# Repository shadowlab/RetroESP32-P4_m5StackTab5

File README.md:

<div align="center">

# 🕹️ RetroESP32-P4

### Fifteen game consoles and native PC-era shooters — on a single ESP32-P4 microcontroller.

**No GPU. No Linux. Bare-metal RISC-V.**

</div>

---

RetroESP32-P4 is an open-source retro-gaming and application platform built on the **ESP32-P4** — a dual-core RISC-V microcontroller with no dedicated GPU. Grown out of a revival of the original [RetroESP32](https://github.com/retro-esp32/RetroESP32), it brings a modern touchscreen launcher, **15 emulators**, and **native apps that execute from PSRAM** — including full Doom and Quake.

The headline: SNES, Genesis/Mega Drive and the mighty **NeoGeo** all run at **60 FPS**.

---

## ✨ Highlights

- 🎮 **15 emulators** — NES through NeoGeo, all with save/load states
- ⚡ **60 FPS** on the 16-bit heavyweights (SNES, Genesis, NeoGeo)
- 🧩 **Native apps from PSRAM** — Doom, Quake, Duke Nukem 3D, OpenTyrian
- 🖥️ **4.3″ touchscreen handheld** — the Guition ESP32-P4 LCD module
- 🎛️ **Any USB gamepad** — auto-detected and auto-mapped on first use
- 💾 **Save states** on every core, some accessible in-game
- 📦 **Everything included** — firmware, source, SD files, apps, PCB, schematic, and case STLs

---

## 🎮 Supported Emulators

| Family | Systems |
|--------|---------|
| **Nintendo** | NES · Game Boy · Game Boy Color · **SNES** ⭐ |
| **Sega** | Master System · Game Gear · **Genesis / Mega Drive** ⭐ |
| **Arcade** | **NeoGeo** ⭐ |

⭐ = hand-tuned to hold **60 FPS** on the P4.

### ⚡ Performance

- Most systems run at **60 FPS with no frame-skip**.
- **SNES / Genesis** — locked 60 FPS via a real-time frame pacer (a handful of *rendered* frames may drop under heavy load; game logic and audio stay at full speed, so play feels perfectly smooth).
- **NeoGeo** — 60 FPS, fully operational, fed by a sprite cache with batched bank prefetch.

### 💾 Save States

**All** emulators support Save / Load states — several directly from the in-game menu.

---

## 🎛️ Controllers

Plug in **any** USB controller and automatic button mapping starts on first use.

---

## 🖥️ Supported Hardware

### 1. Guition ESP32-P4 4.3″ LCD — the handheld

A single [480×800 touchscreen module](https://www.guition.com/esp32p4-display-module/esp32p4-display) becomes a full handheld (the one pictured up top, in a 3D-printed shell). Available on AliExpress or from Guition.

### 2. M5Stack Tab5 — the tablet

The **M5Stack Tab5** (ESP32-P4, 5″ 720×1280 touchscreen, USB-A host port) is supported as a second target. The
launcher and emulators render straight into the panel's DSI frame buffer (UI 1.25×, emulators 3×), with an
**on-screen touch pad** (D-pad, A/B/X/Y, L/R, Start/Select, Menu, Volume) in the side bars; USB controllers
work too. Not yet verified on real hardware — see **[TAB5.md](TAB5.md)** for the
hardware map, build steps (`./build_all_tab5.sh`) and a first-boot checklist.

> **Update the ESP32-C6 first.** Before flashing RetroESP on a Tab5, run the separate
> [tab5-p4-c6-sdio-ota](https://github.com/shadowlab/tab5-p4-c6-sdio-ota) updater, which flashes a matching ESP-Hosted 3.x firmware into the C6
> over SDIO. It is its own application, not part of this build: flash it on its own, wait for `[PASS]`, then
> flash RetroESP.

---

## 🧩 Native Apps from PSRAM

Beyond emulators, RetroESP32-P4 runs **native** applications. A compact app format (**PAPP**) loads binaries off the SD card, memory-maps them into PSRAM, and executes them in place through a shared, versioned service ABI — so you can add apps **without reflashing firmware**.

Included:

- **Doom**
- **Quake**
- **Duke Nukem 3D**
- **OpenTyrian**
- Example demo template (build your own)

---

## 🚀 Getting Started

1. Format an SD card to **FAT32**.
2. Copy the contents of **`/SDCARD`** onto it.
3. Build the merged firmware image and flash it to address **`0`** using the [web esptool](https://espressif.github.io/esptool-js/)
   (prebuilt images are no longer kept in the repository):
   - **`RetroESP32_P4_v1.bin`** — handheld / LCD build (`build_all.ps1`)
4. Insert the SD card.
5. Connect a USB controller (or use the built-in console frame).
6. **NeoGeo only:** run the included Python script once to generate the sprite-cache files (script is in the SD-card folder).
7. Power on, pick a system, and play. 🎉

---

## 🧠 Under the Hood

- **One image per emulator** — each core is its own OTA flash partition; the launcher switches the active partition and reboots straight into the game, so every emulator gets the whole chip.
- **PPA hardware scaler** — with no GPU, the P4's on-chip 2D Pixel-Processing Accelerator handles rotation, scaling and format conversion.
- **Execute-in-place apps** — the PAPP loader maps SD-card binaries into PSRAM and calls them through a service vtable.
- **Dual-core scheduling** — hot paths pinned to internal SRAM/IRAM; the second core carries audio and display so game logic keeps pace.

**Silicon:** ESP32-P4 · dual-core RISC-V @ 360 MHz · 32 MB PSRAM · 16 MB flash.

---

## 📦 Repository Contents

- Firmware build scripts
- Full source code
- SD-card files
- Native apps + PAPP template
- Console board production files and schematic
- Case STL files
- **Link to a folder with all needed**: https://drive.google.com/drive/folders/1b3OWLKbuuy3KIyPls8iDnDMXTKGiJoFR?usp=sharing

---

## 🔧 Roadmap

- More emulators
- Better performance
- More native apps
- Improved UI
- Wi-Fi features
- BLE controllers

---

## 🙌 Contributing

This is only **Version 1**. Suggestions, testing results, and pull requests are all welcome. If you build one, share a photo!

---

## 📜 Credits

Based on the original **RetroESP32** project, revived and modernized for the ESP32-P4. With thanks to:

- The original RetroESP32 authors
- The creator of the ESP32-based Atari 800 emulator
- The SNES and Genesis core authors
- The author of the NeoGeo (gngeo) Linux port

## 📄 License

MIT License.

## ⭐ Support

If you like this project:

- ⭐ **Star** the repo
- 🍴 **Fork** it
- 🧑‍💻 **Contribute**

---

> RetroESP32-P4 isn't just another emulator project — it's a demonstration of how far a modern microcontroller can go when it's optimized correctly.

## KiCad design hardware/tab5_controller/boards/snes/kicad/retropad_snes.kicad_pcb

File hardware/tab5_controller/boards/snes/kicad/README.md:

# SNES board — KiCad PCB

A complete KiCad project for the SNES RetroPad (console ID 3): a schematic and a two-layer,
fully routed board, linked to each other. It was made with KiCad 7 and opens in KiCad 7, 8 and
9.

| File | What it is |
|---|---|
| `retropad_snes.kicad_pro` | The KiCad project; open this |
| `retropad_snes.kicad_sch` / `retropad_snes_schematic.pdf` | Schematic (one A3 sheet) and a PDF of it |
| `retropad_snes.kicad_pcb` | The routed board |
| `retropad_snes_bom.csv` | Bill of materials. R8 and R9 are listed as DNP (not fitted). |
| `retropad_snes_drc.rpt` | KiCad DRC report for this board |
| [`../../kicad_gen/`](../../kicad_gen) | Shared generators: `gen_pcb.py`, `gen_sch.py`, `check_netlist.py` and `gen_avrdd_pinmap.py` for every console board |

## What's on it

* **Front:** 13 switches.
  * D-pad, SELECT, START and MENU: 6×6 tact switches.
  * A, B, X, Y: 12×12 tact switches at 45°.
  * L and R: right-angle 6×6 switches (PTS645 footprint) whose actuators come out of the side
    edges.
  * The 2×5 right-angle header J1 to the Tab5. Its pins point up out of the top edge, centred
    26 mm from the left edge.
* **Back:**
  * AVR32DD28-I/SO (SOIC-28) with 100 nF on each VDD pin and on VDDIO2, 4.7 µF bulk, 4.7 k
    I2C pull-ups and a 10 k RESET pull-up.
  * Console-ID resistors R6–R9: 0 Ω on ID0 and ID1 for SNES, R8 and R9 not fitted.
  * UPDI header J2: 3V3, UPDI, GND.
* **Buttons:** each switch connects its own MCU pin to GND, with the MCU's internal pull-up.
  No matrix, no diodes. The 6×6 and 12×12 switches use all four legs: 1–2 to GND, 3–4 to the
  MCU pin (see [Switches](../../README.md#switches)); L and R have two contacts. The slot order (PD1–PD7, PC0–PC3, PF0–PF1) follows the layout's
  button order and matches `firmware_avrdd/pinmap.h`; the table is in
  [`../README.md`](../README.md#pcb-and-schematic). J1 pin 9 (INT) and pin 10 (G9) are not
  connected; the host polls.
* **Outline:**
  * 125 × 55 mm, inset 1.5 mm from the case on each side.
  * Notched 3 mm in at the top corners above y = 46 to clear the latch arms.
  * Two M3 holes, 96 mm apart.
* **Stack-up and rules:**
  * 2 layers, 1.6 mm.
  * 0.25 mm tracks, 0.2 mm clearance, 0.6/0.3 mm vias, 0.3 mm copper-to-edge.
  * GND pour on both layers.

## Checks run

* **DRC:** 0 unconnected pads and no clearance, short or edge errors. The report still lists
  silkscreen warnings (labels overlapping pads or running past the edge where L/R overhang),
  plus "library not configured" notes that only appear on a machine without KiCad's library
  table. All are cosmetic.
* **Schematic vs board:** `check_netlist.py` reports the same 25 nets on each side with 0
  differences.
* **Wiring vs firmware:** every switch lands on the MCU pin the firmware's pin map gives it
  for console ID 3, the straps encode ID 3, and J1 carries M5Stack's P1 pinout.
* **Gerber and drill export:** both succeed.

## Schematic

The schematic covers the same circuit on one A3 sheet:
* **MCU:** the AVR32DD28. KiCad 7 has no AVR DD symbol, so the schematic embeds one derived
  from the pin-compatible AVR32DB28, with pins 13/14/15/19 renamed (PD7, VDD, GND, UPDI/PF7).
* **Tab5 header and UPDI header.**
* **Support parts:** decoupling, I2C pull-ups and the RESET pull-up.
* **Console-ID straps:** R8 and R9 are marked DNP.
* **Mounting holes.**
* **Buttons:** one line per button. 4-leg switches show all four pins: 1–2 to GND, 4–3 to
  K_<button>. L and R are 2-pin: K_<button> → switch → GND.

Nets are named with global labels, so the net names match the board exactly (K_UP and so on,
SCL, SDA, ID0–ID3, AN0/AN1, RESET, UPDI, +3V3, GND).

How it stays in step with the board:
* `gen_sch.py` doesn't keep its own list of connections. It builds the board in memory
  and gives each symbol pin the net of the footprint pad with the same number.
* Each footprint carries its symbol's UUID, so in KiCad **Tools → Update PCB from
  Schematic** matches every part and reports no changes.
* `check_netlist.py snes` exports the schematic netlist with `kicad-cli` and compares it with the
  board pad by pad. Current result: 25 nets on each side, 0 differences.

You can now edit the design in KiCad the normal way, schematic first. Just remember that
re-running the generator scripts overwrites the `.kicad_sch` and `.kicad_pcb` files. Once you
start editing by hand, treat the scripts as the starting point and stop re-running them.

KiCad 7's command line has no ERC, so ERC hasn't been run. When you open the schematic, run
**Inspect → Electrical Rules Checker** once. Expect only notes about the power pins being
driven from the connector (J1 has no power-flag symbol).

## ⚠ Before ordering

These can't be settled from M5Stack's drawings, and getting the first one wrong could put
the Tab5's 5 V rail (pin 6) onto this board's 3.3 V supply:

1. **J1 orientation.** The two header rows end up at different heights once the pins are bent
   up, and either end of the 5-pin row could be pin 1. On a real keyboard, use a multimeter to
   find **pin 5 (3V3)**: it connects to the keyboard MCU's VDD pins and the 100 nF capacitors. Also
   find **pins 2/3/4 (GND)**. Note which physical pin positions they are, seen from the front,
   and compare with J1's pin 1 marker here. In the board as drawn, pin 1 is the lower-left pin
   (front view) and the odd row is the one farther from the edge. If yours differs, flip
   `HEADER_PINS` or the header rotation in `../../kicad_gen/gen_pcb.py` (shared by every board) and regenerate.
2. **J1 height and side.** The header sits on the front side, with the pin rows about 1.5 mm
   and 4 mm above the board. Check that this matches where the Tab5's socket is once the shell
   is designed.
3. **M3 hole height** (`M3_Y`, now 45 mm, an estimate) and **latch-arm length** (the board
   notch starts at y = 46).
4. **L/R switch part.** The footprint is C&K PTS645Vx31 (right-angle). Check the actuator
   length against your shell wall, and design the side openings to match.

## Regenerating

See [`../../README.md`](../../README.md#regenerating). For this board:

```
cd ../../kicad_gen
FREEROUTING_JAR=/path/to/freerouting-1.9.0.jar python3 gen_pcb.py snes --route
python3 gen_sch.py snes
python3 check_netlist.py snes          # schematic vs board: must report 0 differences
```

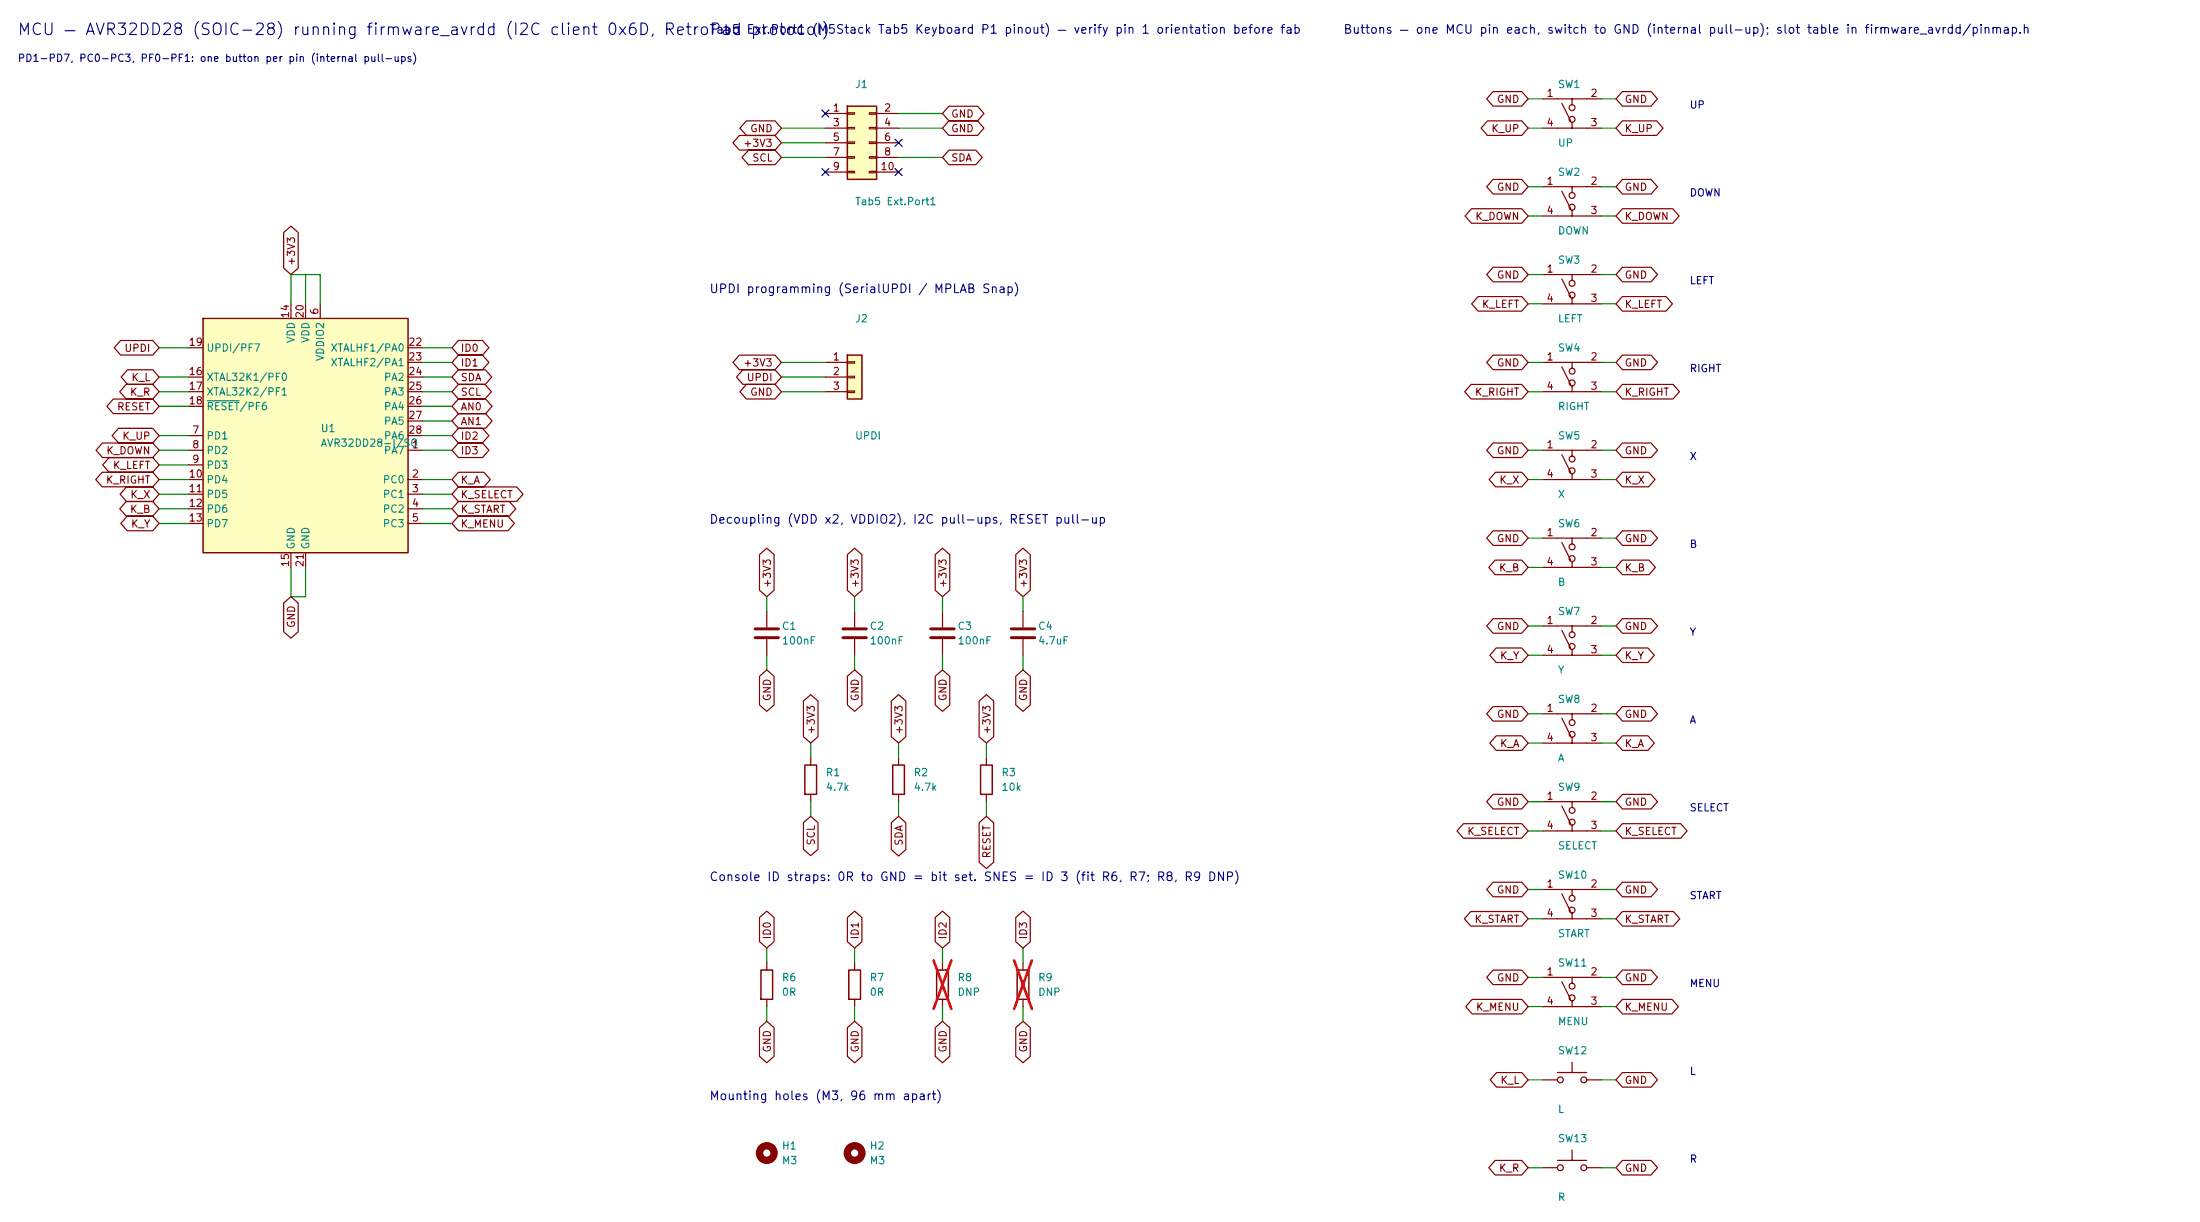
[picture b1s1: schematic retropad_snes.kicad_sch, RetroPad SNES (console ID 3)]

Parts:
C1, C2, C3: 100nF; C_0805_2012Metric_Pad1.18x1.45mm_HandSolder
C4: 4.7uF; C_0805_2012Metric_Pad1.18x1.45mm_HandSolder
H1, H2: M3; MountingHole_3.2mm_M3
J1: Tab5 Ext.Port1; PinHeader_2x05_P2.54mm_Horizontal
J2: UPDI; PinHeader_1x03_P2.54mm_Vertical
R1, R2: 4.7k; R_0805_2012Metric_Pad1.20x1.40mm_HandSolder
R3: 10k; R_0805_2012Metric_Pad1.20x1.40mm_HandSolder
R6, R7: 0R; R_0805_2012Metric_Pad1.20x1.40mm_HandSolder
R8, R9: DNP; R_0805_2012Metric_Pad1.20x1.40mm_HandSolder; not fitted
SW1: UP; SW_PUSH_6mm_4pin
SW2: DOWN; SW_PUSH_6mm_4pin
SW3: LEFT; SW_PUSH_6mm_4pin
SW4: RIGHT; SW_PUSH_6mm_4pin
SW5: X; SW_PUSH-12mm_4pin
SW6: B; SW_PUSH-12mm_4pin
SW7: Y; SW_PUSH-12mm_4pin
SW8: A; SW_PUSH-12mm_4pin
SW9: SELECT; SW_PUSH_6mm_4pin
SW10: START; SW_PUSH_6mm_4pin
SW11: MENU; SW_PUSH_6mm_4pin
SW12: L; SW_Tactile_SPST_Angled_PTS645Vx31-2LFS
SW13: R; SW_Tactile_SPST_Angled_PTS645Vx31-2LFS
U1: AVR32DD28-I/SO; SOIC-28W_7.5x17.9mm_P1.27mm

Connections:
+3V3: C1.1, C2.1, C3.1, C4.1, J1.5, J2.1, R1.1, R2.1, R3.1, U1.6 (VDDIO2), U1.14 (VDD), U1.20 (VDD)
AN0: U1.26 (PA4)
AN1: U1.27 (PA5)
GND: C1.2, C2.2, C3.2, C4.2, J1.2, J1.3, J1.4, J2.3, R6.2, R7.2, R8.2, R9.2, SW1.1, SW1.2, SW2.1, SW2.2, SW3.1, SW3.2, SW4.1, SW4.2, SW5.1, SW5.2, SW6.1, SW6.2, SW7.1, SW7.2, SW8.1, SW8.2, SW9.1, SW9.2, SW10.1, SW10.2, SW11.1, SW11.2, SW12.2, SW13.2, U1.15 (GND), U1.21 (GND)
ID0: R6.1, U1.22 (XTALHF1/PA0)
ID1: R7.1, U1.23 (XTALHF2/PA1)
ID2: R8.1, U1.28 (PA6)
ID3: R9.1, U1.1 (PA7)
K_A: SW8.3, SW8.4, U1.2 (PC0)
K_B: SW6.3, SW6.4, U1.12 (PD6)
K_DOWN: SW2.3, SW2.4, U1.8 (PD2)
K_L: SW12.1, U1.16 (XTAL32K1/PF0)
K_LEFT: SW3.3, SW3.4, U1.9 (PD3)
K_MENU: SW11.3, SW11.4, U1.5 (PC3)
K_R: SW13.1, U1.17 (XTAL32K2/PF1)
K_RIGHT: SW4.3, SW4.4, U1.10 (PD4)
K_SELECT: SW9.3, SW9.4, U1.3 (PC1)
K_START: SW10.3, SW10.4, U1.4 (PC2)
K_UP: SW1.3, SW1.4, U1.7 (PD1)
K_X: SW5.3, SW5.4, U1.11 (PD5)
K_Y: SW7.3, SW7.4, U1.13 (PD7)
RESET: R3.2, U1.18 (~RESET/PF6)
SCL: J1.7, R1.2, U1.25 (PA3)
SDA: J1.8, R2.2, U1.24 (PA2)
UPDI: J2.2, U1.19 (UPDI/PF7)

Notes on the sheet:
MCU — AVR32DD28 (SOIC-28) running firmware_avrdd (I2C client 0x6D, RetroPad protocol)
PD1-PD7, PC0-PC3, PF0-PF1: one button per pin (internal pull-ups)
Tab5 Ext.Port1 (M5Stack Tab5 Keyboard P1 pinout) — verify pin 1 orientation before fab
UPDI programming (SerialUPDI / MPLAB Snap)
Decoupling (VDD x2, VDDIO2), I2C pull-ups, RESET pull-up
Console ID straps: 0R to GND = bit set. SNES = ID 3 (fit R6, R7; R8, R9 DNP)
Mounting holes (M3, 96 mm apart)
Buttons — one MCU pin each, switch to GND (internal pull-up); slot table in firmware_avrdd/pinmap.h
DOWN
LEFT
RIGHT
SELECT
START
MENU

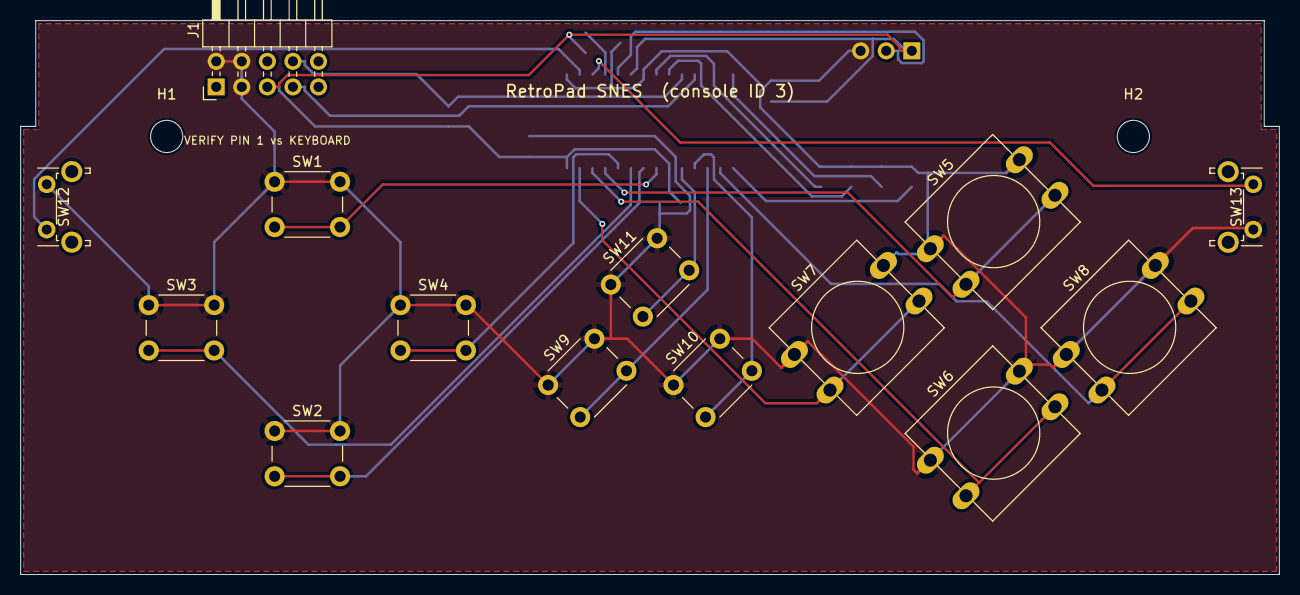
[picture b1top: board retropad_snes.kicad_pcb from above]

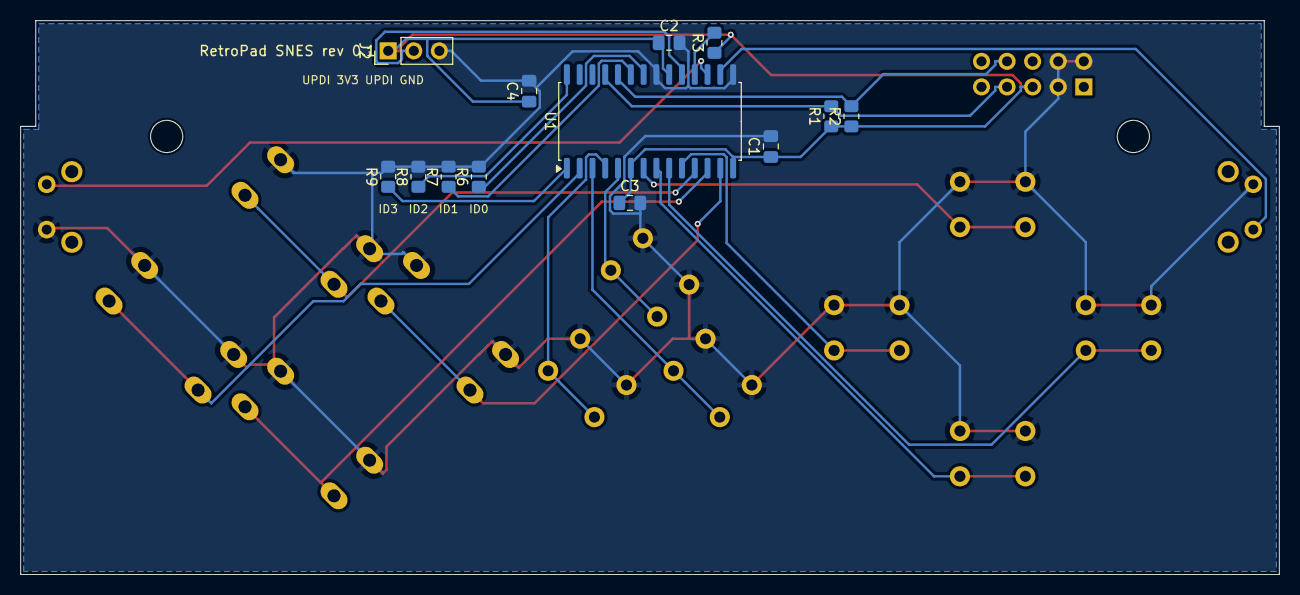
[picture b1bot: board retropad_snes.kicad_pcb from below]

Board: 2 copper layers, 125.0 x 55.0 mm, 29 parts (13 on the bottom side), 23 nets.

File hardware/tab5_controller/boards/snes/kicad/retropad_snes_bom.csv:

Qty,References,Value,Footprint,Side,Fit,Manufacturer,MPN,DigiKey
3,C1 C2 C3,100nF,C_0805_2012Metric_Pad1.18x1.45mm_HandSolder,back,yes,,,
1,C4,4.7uF,C_0805_2012Metric_Pad1.18x1.45mm_HandSolder,back,yes,,,
1,J1,Tab5 Ext.Port1,PinHeader_2x05_P2.54mm_Horizontal,front,yes,Samtec,TSW-105-08-G-D-RA,SAM1037-05-ND
1,J2,UPDI,PinHeader_1x03_P2.54mm_Vertical,back,yes,,,
2,R1 R2,4.7k,R_0805_2012Metric_Pad1.20x1.40mm_HandSolder,back,yes,,,
1,R3,10k,R_0805_2012Metric_Pad1.20x1.40mm_HandSolder,back,yes,,,
2,R6 R7,0R,R_0805_2012Metric_Pad1.20x1.40mm_HandSolder,back,yes,,,
0,R8 R9,DNP,R_0805_2012Metric_Pad1.20x1.40mm_HandSolder,back,DNP,,,
1,SW1,UP,SW_PUSH_6mm_4pin,front,yes,C&K,PTS645SM43-2 LFS,
1,SW2,DOWN,SW_PUSH_6mm_4pin,front,yes,C&K,PTS645SM43-2 LFS,
1,SW3,LEFT,SW_PUSH_6mm_4pin,front,yes,C&K,PTS645SM43-2 LFS,
1,SW4,RIGHT,SW_PUSH_6mm_4pin,front,yes,C&K,PTS645SM43-2 LFS,
1,SW5,X,SW_PUSH-12mm_4pin,front,yes,Omron,B3F-4055,SW414-ND
1,SW6,B,SW_PUSH-12mm_4pin,front,yes,Omron,B3F-4055,SW414-ND
1,SW7,Y,SW_PUSH-12mm_4pin,front,yes,Omron,B3F-4055,SW414-ND
1,SW8,A,SW_PUSH-12mm_4pin,front,yes,Omron,B3F-4055,SW414-ND
1,SW9,SELECT,SW_PUSH_6mm_4pin,front,yes,C&K,PTS645SM43-2 LFS,
1,SW10,START,SW_PUSH_6mm_4pin,front,yes,C&K,PTS645SM43-2 LFS,
1,SW11,MENU,SW_PUSH_6mm_4pin,front,yes,C&K,PTS645SM43-2 LFS,
1,SW12,L,SW_Tactile_SPST_Angled_PTS645Vx31-2LFS,front,yes,C&K,PTS645VL31-2 LFS,CKN9094-ND
1,SW13,R,SW_Tactile_SPST_Angled_PTS645Vx31-2LFS,front,yes,C&K,PTS645VL31-2 LFS,CKN9094-ND
1,U1,AVR32DD28-I/SO,SOIC-28W_7.5x17.9mm_P1.27mm,back,yes,,,

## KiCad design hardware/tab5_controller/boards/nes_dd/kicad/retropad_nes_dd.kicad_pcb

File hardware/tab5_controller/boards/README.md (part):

# RetroPad console boards

Each board is a console-specific controller PCB that fits where the M5Stack Tab5 Keyboard
goes. Every board:
* uses the same AVR32DD28 (SOIC-28), 2×5 Tab5 header and register protocol (see
  [`../README.md`](../README.md));
* wires each button to its own MCU pin (switch to GND, internal pull-up), so there is no key
  matrix and no diodes;
* runs the same firmware, [`../firmware_avrdd`](../firmware_avrdd), programmed over UPDI;
* uses 0805 resistors and capacitors with KiCad's hand-solder pads, so the boards can be
  assembled by hand;
* identifies itself through its console-ID straps, so the firmware maps its buttons for the
  emulator that is running.

| Board | Console ID | Buttons | Layout | KiCad project |
|---|---|---|---|---|
| [SNES](snes/README.md) | 3 | D-pad, A B X Y, L R (side edges), SELECT START, MENU | [svg](snes/layout.svg) | [`snes/kicad`](snes/kicad) |
| [NES / Game Boy / Master System](nes_gb_sms/README.md) | 1, 2 or 4 (CONSOLE button) | D-pad, B A (A raised 4 mm), SELECT START, MENU | [svg](nes_gb_sms/layout.svg) | [`nes_gb_sms/kicad`](nes_gb_sms/kicad) |
| [Genesis / Mega Drive 6-button](genesis/README.md) | 5 | D-pad, X Y Z over A B C, MODE START, MENU | [svg](genesis/layout.svg) | [`genesis/kicad`](genesis/kicad) |

Every KiCad project:
* is a schematic plus a routed, two-layer, 125 × 55 mm PCB;
* passes DRC with 0 unconnected pads and no clearance, short or edge errors (only silkscreen
  warnings remain);
* has a schematic that matches its PCB net for net (`check_netlist.py`).

The SNES layout follows the user's reference drawing. The NES / Game Boy / Master System and
Genesis (6-button) layouts follow each console's own pad, scaled the same way. X/Y/Z/MODE on the
Genesis board reach games through the Genesis core's 6-button support (`components/gwenesis`,
merged from https://github.com/shadowlab/RetroESP32-P4_m5StackTab5/pull/4). The NES / Game Boy / Master System
board puts A 4 mm above B, between the NES pad's level buttons and the Game Boy's diagonal, and
picks its console with a button and an RGB LED (see [Console select](#console-select)).

## How the boards are made

| File | Role |
|---|---|
| [`layout.py`](layout.py) | Button positions for every console, the console IDs, and clearance checks (switch bodies, pads, footprint courtyards, M3 holes, wall margin, latch arms). It also draws `<console>/layout.svg`. |
| [`kicad_gen/gen_pcb.py`](kicad_gen/gen_pcb.py) | Builds the PCB: switches and the 2×5 header on the front; MCU, support parts, console-ID straps and the UPDI header on the back. It routes with Freerouting, pours GND, runs DRC and writes a BOM. |
| [`kicad_gen/gen_sch.py`](kicad_gen/gen_sch.py) | Builds the schematic from the same board data, so it can't drift from the PCB. Every net, GND and +3V3 included, is a global label rather than a KiCad power symbol, so EasyEDA's import keeps the names (it would turn `power:GND` into `power_GND`). |
| [`kicad_gen/check_netlist.py`](kicad_gen/check_netlist.py) | Compares the schematic netlist with the PCB pad by pad |
| [`kicad_gen/render.py`](kicad_gen/render.py) | Writes the front/back/schematic PNGs and the schematic PDF |
| [`kicad_gen/gen_avrdd_pinmap.py`](kicad_gen/gen_avrdd_pinmap.py) | Writes `../firmware_avrdd/pinmap.h`, the per-console button slot table |
| [`kicad_lib/RetroPad.pretty`](kicad_lib/RetroPad.pretty) | 4-pin tact-switch footprints, written by `gen_pcb.py` (see [Switches](#switches)) |

A board has 13 button slots (PD1–PD7, PC0–PC3, PF0–PF1). A console's buttons fill them in
the order its layout lists them. `gen_pcb.py` wires that order, and `gen_avrdd_pinmap.py`
writes it into the firmware's pin map, keyed by console ID. The firmware is therefore the same
for every console; only the ID straps differ.

### Switches

The 6×6 and 12×12 tact switches are 4-leg parts, so the schematics and footprints use all
four pins, numbered like the parts' own symbols:

```
  1 ───┬─── 2      1–2: tied inside the switch  → GND
       /
  4 ───┴─── 3      4–3: tied inside the switch  → K_<button> (MCU pin)
```

* **Footprints:** `RetroPad:SW_PUSH_6mm_4pin` and `RetroPad:SW_PUSH-12mm_4pin` are KiCad's
  `SW_PUSH_6mm` / `SW_PUSH-12mm` with the pads renumbered 1–4. Pad 1 is top-left, then
  clockwise. The tied pairs are the legs 6.5 mm (12.5 mm) apart, as in KiCad's original
  numbering.
* **Symbol:** `RetroPad:SW_Push_4pin`, embedded in each schematic. KiCad's own 4-pin
  `Switch:SW_Push_Dual` is a two-contact switch (1–2 and 3–4 each switched), so it doesn't
  match these parts.
* **L / R (right angle):** two contacts plus two mounting legs, so they keep KiCad's 2-pin
  `SW_Push` and the stock PTS645Vx31 footprint.
* **Other EDA tools:** a vendor's own symbol and footprint can number the legs differently, and
  some parts tie 1–3 / 2–4 instead. Before wiring a part, check its datasheet's
  internal-connection drawing. GND and the MCU pin must go to opposite sides of the contact.
  If they share a tied pair, the button always reads as pressed.

Each board's `kicad/fp-lib-table` points KiCad at `kicad_lib/RetroPad.pretty`.

### Console select

The NES / Game Boy / Master System board serves three consoles. Its ID straps read 14
(`SELECT_STRAP_ID`, never reported to the Tab5), which puts the firmware in select mode:

* **CONSOLE button** (SW_SEL, 6×6 tact switch, front, below SELECT/START) on PC3. Each press
  steps NES (1) → Game Boy (2) → Master System (4) → NES. The firmware reports the new console ID
  at once, and the Tab5 driver re-reads it every 250 ms, so it switches the button map and the
  launcher jumps to that console's games. The choice is saved in EEPROM and restored at power-up
  (a blank EEPROM starts on NES).
* **Status LED** (LED1, OPSCO SK6812MINI-E, reverse mount) shows the console: red = NES,
  green = Game Boy, blue = Master System, at about 16% brightness. It is soldered on the back and
  shines through a 3.3 × 2.9 mm board cutout beside the button. The pads follow the datasheet's
  recommended land pattern (1.8 × 0.82 mm, 0.68 mm gap); a keepout keeps tracks 0.5 mm clear of
  the cutout.
* **LED power:** the SK6812 needs 3.7–5.5 V, so LED1 runs from the Tab5's 5 V (J1 pin 6, unused
  on the other boards) through D1 (1N4148W). The ~4.3 V that leaves lowers the LED's input
  threshold (0.7 × VDD ≈ 3.0 V) enough for the 3.3 V AVR to drive DIN (PC2, through R10 100 Ω)
  in spec. C5 (100 nF) decouples it. The rest of the board stays on 3.3 V; without 5 V on the
  header only the LED stays dark.
* **Timing:** the firmware bit-bangs the LED from a short assembly loop at 24 MHz (0 = 0.29 µs
  high, 1 = 0.63 µs high, 1.25 µs per bit) with interrupts off for about 35 µs. The I2C client
  stretches the clock meanwhile. The colour is re-sent every second in case the LED powered up
  after the MCU.

The console list and colours live in `CONSOLE_SELECT` in `layout.py`; `gen_avrdd_pinmap.py`
copies them into `firmware_avrdd/pinmap.h`.

### Regenerating

```
sudo apt install kicad xvfb default-jre            # KiCad 7+ (with its Python module), Java, virtual display
pip install cairosvg pillow                        # only for render.py
curl -LO https://github.com/freerouting/freerouting/releases/download/v1.9.0/freerouting-1.9.0.jar

cd kicad_gen
export FREEROUTING_JAR=$PWD/../freerouting-1.9.0.jar
for c in snes nes_gb_sms genesis; do
  python3 gen_pcb.py $c --route      # FR_PASSES=300 for more router passes
  python3 gen_sch.py $c
  python3 check_netlist.py $c        # must report 0 differences
  python3 render.py $c
done
python3 gen_avrdd_pinmap.py          # after changing a layout's buttons
```

Freerouting 1.9 runs single-threaded on purpose. In testing, 2.1's multi-threaded optimiser
reported "0 unrouted" but wrote a session with nets missing.

Two changes keep the boards intact through EasyEDA's KiCad import (KiCad shows no difference):
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
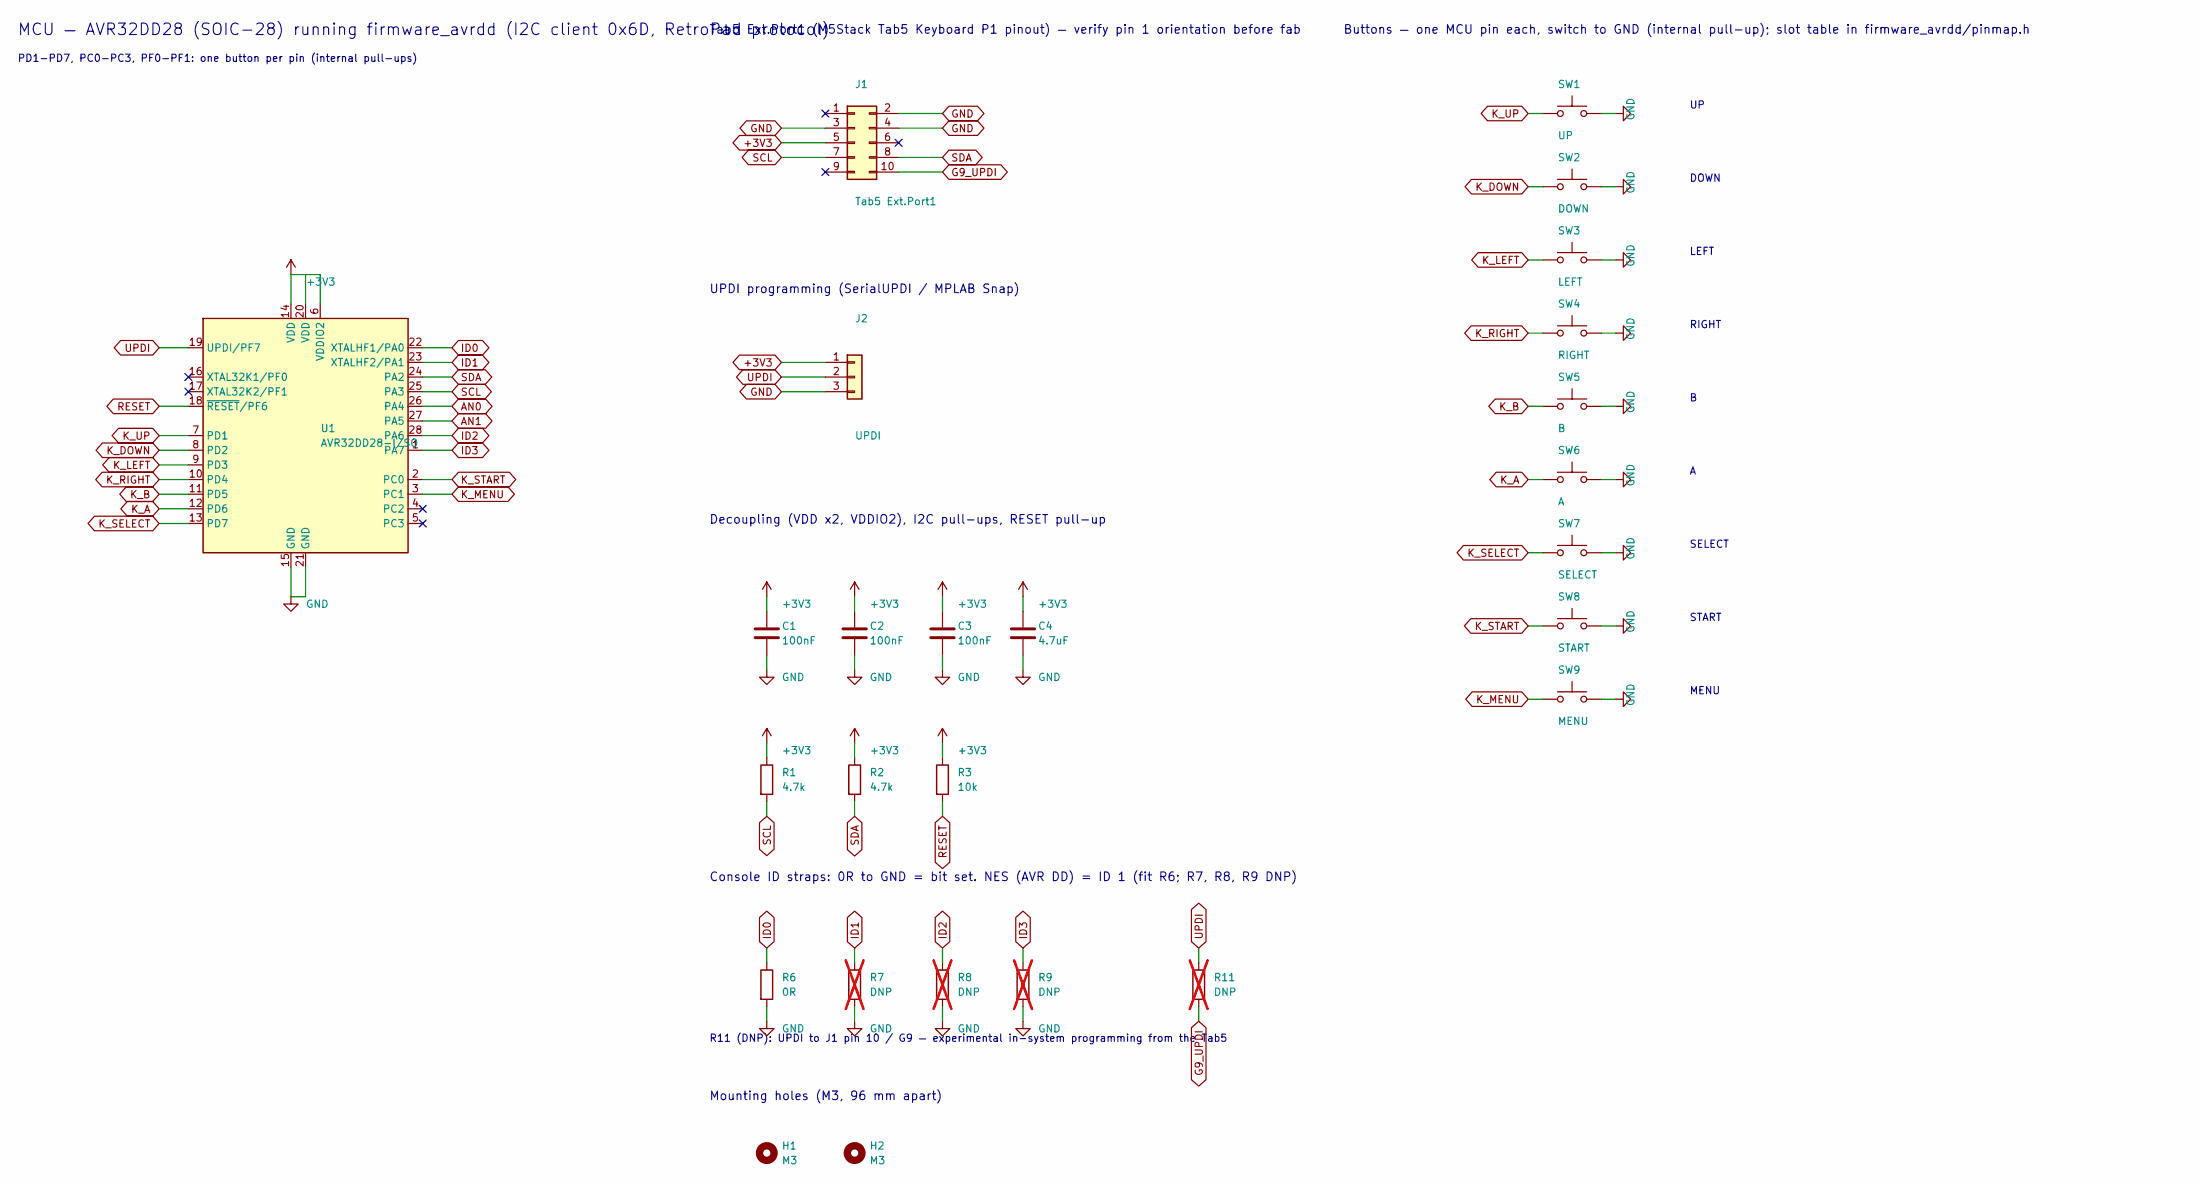
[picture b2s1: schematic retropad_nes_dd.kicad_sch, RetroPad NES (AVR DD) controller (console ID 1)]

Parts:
C1, C2, C3: 100nF; C_0603_1608Metric
C4: 4.7uF; C_0603_1608Metric
H1, H2: M3; MountingHole_3.2mm_M3
J1: Tab5 Ext.Port1; PinHeader_2x05_P2.54mm_Horizontal
J2: UPDI; PinHeader_1x03_P2.54mm_Vertical
R1, R2: 4.7k; R_0603_1608Metric
R3: 10k; R_0603_1608Metric
R6: 0R; R_0603_1608Metric
R7, R8, R9, R11: DNP; R_0603_1608Metric; not fitted
SW1: UP; SW_PUSH_6mm
SW2: DOWN; SW_PUSH_6mm
SW3: LEFT; SW_PUSH_6mm
SW4: RIGHT; SW_PUSH_6mm
SW5: B; SW_PUSH-12mm
SW6: A; SW_PUSH-12mm
SW7: SELECT; SW_PUSH_6mm
SW8: START; SW_PUSH_6mm
SW9: MENU; SW_PUSH_6mm
U1: AVR32DD28-I/SO; SOIC-28W_7.5x17.9mm_P1.27mm

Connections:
+3V3: C1.1, C2.1, C3.1, C4.1, J1.5, J2.1, R1.1, R2.1, R3.1, U1.6 (VDDIO2), U1.14 (VDD), U1.20 (VDD)
AN0: U1.26 (PA4)
AN1: U1.27 (PA5)
G9_UPDI: J1.10, R11.2
GND: C1.2, C2.2, C3.2, C4.2, J1.2, J1.3, J1.4, J2.3, R6.2, R7.2, R8.2, R9.2, SW1.2, SW2.2, SW3.2, SW4.2, SW5.2, SW6.2, SW7.2, SW8.2, SW9.2, U1.15 (GND), U1.21 (GND)
ID0: R6.1, U1.22 (XTALHF1/PA0)
ID1: R7.1, U1.23 (XTALHF2/PA1)
ID2: R8.1, U1.28 (PA6)
ID3: R9.1, U1.1 (PA7)
K_A: SW6.1, U1.12 (PD6)
K_B: SW5.1, U1.11 (PD5)
K_DOWN: SW2.1, U1.8 (PD2)
K_LEFT: SW3.1, U1.9 (PD3)
K_MENU: SW9.1, U1.3 (PC1)
K_RIGHT: SW4.1, U1.10 (PD4)
K_SELECT: SW7.1, U1.13 (PD7)
K_START: SW8.1, U1.2 (PC0)
K_UP: SW1.1, U1.7 (PD1)
RESET: R3.2, U1.18 (~RESET/PF6)
SCL: J1.7, R1.2, U1.25 (PA3)
SDA: J1.8, R2.2, U1.24 (PA2)
UPDI: J2.2, R11.1, U1.19 (UPDI/PF7)

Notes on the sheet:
MCU — AVR32DD28 (SOIC-28) running firmware_avrdd (I2C client 0x6D, RetroPad protocol)
PD1-PD7, PC0-PC3, PF0-PF1: one button per pin (internal pull-ups)
Tab5 Ext.Port1 (M5Stack Tab5 Keyboard P1 pinout) — verify pin 1 orientation before fab
UPDI programming (SerialUPDI / MPLAB Snap)
Decoupling (VDD x2, VDDIO2), I2C pull-ups, RESET pull-up
Console ID straps: 0R to GND = bit set. NES (AVR DD) = ID 1 (fit R6; R7, R8, R9 DNP)
R11 (DNP): UPDI to J1 pin 10 / G9 — experimental in-system programming from the Tab5
Mounting holes (M3, 96 mm apart)
Buttons — one MCU pin each, switch to GND (internal pull-up); slot table in firmware_avrdd/pinmap.h
DOWN
LEFT
RIGHT
SELECT
START
MENU

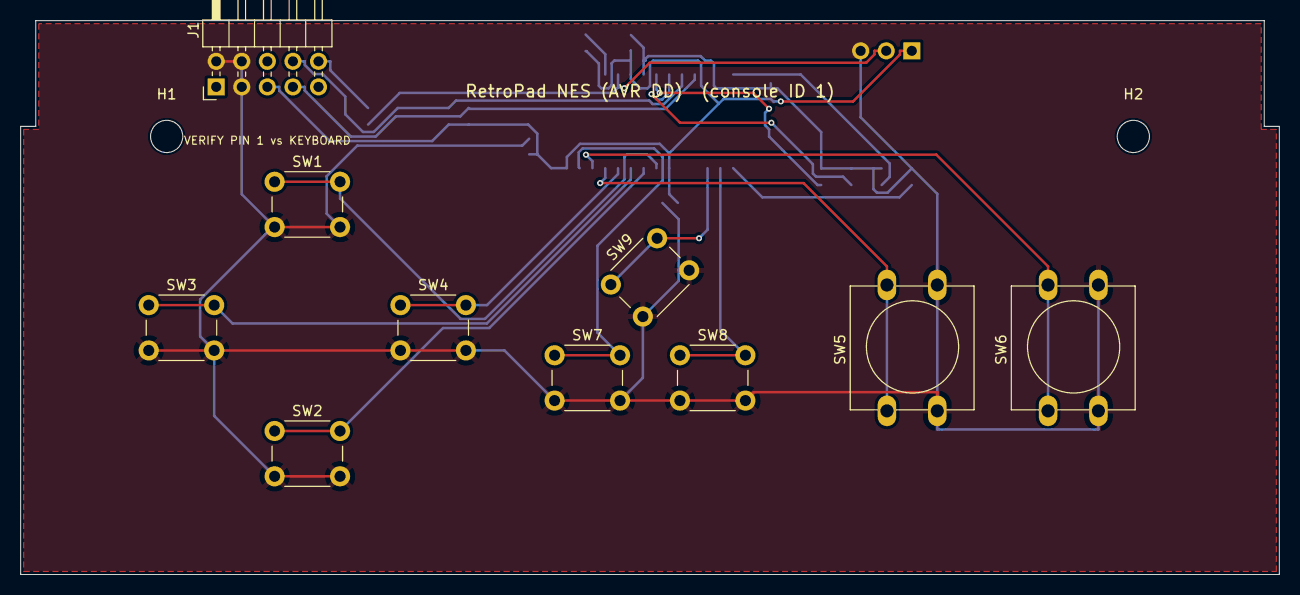
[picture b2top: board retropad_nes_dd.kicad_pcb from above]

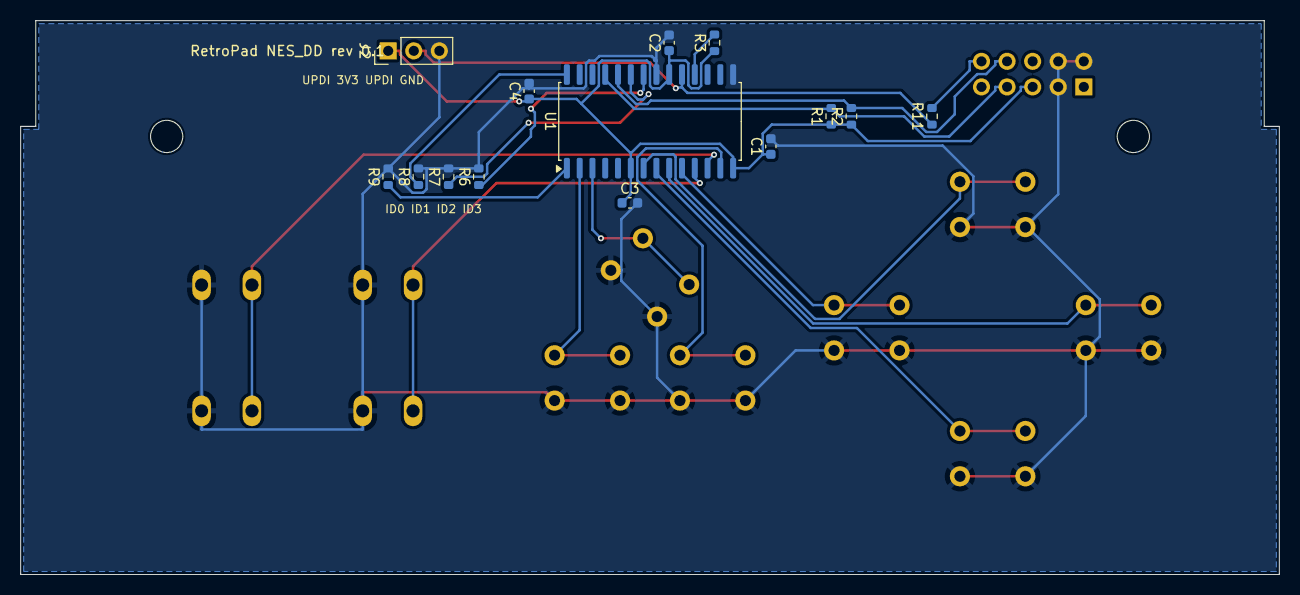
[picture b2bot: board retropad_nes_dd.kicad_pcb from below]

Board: 2 copper layers, 125.0 x 55.0 mm, 26 parts (14 on the bottom side), 20 nets.

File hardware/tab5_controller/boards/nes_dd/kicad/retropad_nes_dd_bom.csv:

Qty,References,Value,Footprint,Side,Fit
3,C1 C2 C3,100nF,C_0603_1608Metric,back,yes
1,C4,4.7uF,C_0603_1608Metric,back,yes
1,J1,Tab5 Ext.Port1,PinHeader_2x05_P2.54mm_Horizontal,front,yes
1,J2,UPDI,PinHeader_1x03_P2.54mm_Vertical,back,yes
2,R1 R2,4.7k,R_0603_1608Metric,back,yes
1,R3,10k,R_0603_1608Metric,back,yes
1,R6,0R,R_0603_1608Metric,back,yes
0,R7 R8 R9 R11,DNP,R_0603_1608Metric,back,DNP
1,SW1,UP,SW_PUSH_6mm,front,yes
1,SW2,DOWN,SW_PUSH_6mm,front,yes
1,SW3,LEFT,SW_PUSH_6mm,front,yes
1,SW4,RIGHT,SW_PUSH_6mm,front,yes
1,SW5,B,SW_PUSH-12mm,front,yes
1,SW6,A,SW_PUSH-12mm,front,yes
1,SW7,SELECT,SW_PUSH_6mm,front,yes
1,SW8,START,SW_PUSH_6mm,front,yes
1,SW9,MENU,SW_PUSH_6mm,front,yes
1,U1,AVR32DD28-I/SO,SOIC-28W_7.5x17.9mm_P1.27mm,back,yes

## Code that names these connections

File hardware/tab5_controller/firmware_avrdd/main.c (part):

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 * keyboard's event/HID/char modes are not.
 *
 * Pins (see boards/layout.py AVRDD_SLOTS and pinmap.h):
 *   PD1-PD7, PC0-PC3, PF0-PF1  13 button slots, switch to GND, internal pull-up
 *   PA2 SDA, PA3 SCL           I2C client to the Tab5 (TWI0 default pins)
 *   PA0, PA1, PA6, PA7         console-ID straps ID0..ID3 (0R to GND = bit set)
 *   PA4, PA5                   AN0 / AN1 (AIN24 / AIN25), Atari paddle/analog boards
 *   PC3, PC2                   console-select boards: select button, SK6812 status LED
 *   PF7 UPDI, PF6 RESET        programming
 */
#include <avr/eeprom.h>
#include <avr/interrupt.h>
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
static uint8_t read_console_id(void)
{
    static const uint8_t strap_pin[4] = {0, 1, 6, 7};     /* PA0, PA1, PA6, PA7 */
    uint8_t id = 0;
    for (uint8_t i = 0; i < 4; i++)
        pullup(&PORTA, strap_pin[i]);
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
/* ── console-select boards (pinmap.h SELECT_*) ─────────────────────────── *
 * Straps reading SELECT_STRAP_ID mark a board shared by several consoles. Each
 * press of the select button (PC3) steps to the next entry of select_console[],
 * which is saved to EEPROM and shown on the SK6812MINI-E on PC2 in that
 * console's colour. The Tab5 re-reads the console ID, so the launcher follows. */
#define SEL_DEBOUNCE_MS 20
#define LED_REFRESH_MS  1000            /* re-send: the LED's 5 V may come up late */
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
static void twi_init(void)
{
    PORTMUX.TWIROUTEA = PORTMUX_TWI0_DEFAULT_gc;             /* SDA PA2, SCL PA3 */
    TWI0.SADDR = RP_I2C_ADDR_DEFAULT << 1;
    TWI0.SCTRLA = TWI_DIEN_bm | TWI_APIEN_bm | TWI_PIEN_bm | TWI_ENABLE_bm;
}
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
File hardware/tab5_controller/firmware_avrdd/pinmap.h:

/* Generated by boards/kicad_gen/gen_avrdd_pinmap.py from boards/layout.py. Do not edit. */
#ifndef RETROPAD_PINMAP_H
#define RETROPAD_PINMAP_H

#include <avr/io.h>
#include "retropad_proto.h"

#define SLOT_COUNT 13
#define SLOT_NONE  0xFF

/* Button slot -> MCU pin (switch to GND, internal pull-up) */
static PORT_t *const slot_port[SLOT_COUNT] = {&PORTD, &PORTD, &PORTD, &PORTD, &PORTD, &PORTD, &PORTD, &PORTC, &PORTC, &PORTC, &PORTC, &PORTF, &PORTF};
static const uint8_t slot_pin[SLOT_COUNT] = {1, 2, 3, 4, 5, 6, 7, 0, 1, 2, 3, 0, 1};

/* Console ID -> RetroPad bit carried by each slot (SLOT_NONE = not fitted) */
static const uint8_t slot_bit[RP_CONSOLE_COUNT][SLOT_COUNT] = {
    /*  0 no board layout yet: generic slot order UP DOWN LEFT RIGHT A B X Y L R SELECT START MENU */
    [0] = {RP_BTN_UP, RP_BTN_DOWN, RP_BTN_LEFT, RP_BTN_RIGHT, RP_BTN_A, RP_BTN_B, RP_BTN_X, RP_BTN_Y, RP_BTN_L, RP_BTN_R, RP_BTN_SELECT, RP_BTN_START, RP_BTN_MENU},
    /*  1 same slots as the NES / Game Boy / Master System board: UP=PD1, DOWN=PD2, LEFT=PD3, RIGHT=PD4, B=PD5, A=PD6, SELECT=PD7, START=PC0, MENU=PC1 */
    [1] = {RP_BTN_UP, RP_BTN_DOWN, RP_BTN_LEFT, RP_BTN_RIGHT, RP_BTN_B, RP_BTN_A, RP_BTN_SELECT, RP_BTN_START, RP_BTN_MENU, SLOT_NONE, SLOT_NONE, SLOT_NONE, SLOT_NONE},
    /*  2 same slots as the NES / Game Boy / Master System board: UP=PD1, DOWN=PD2, LEFT=PD3, RIGHT=PD4, B=PD5, A=PD6, SELECT=PD7, START=PC0, MENU=PC1 */
    [2] = {RP_BTN_UP, RP_BTN_DOWN, RP_BTN_LEFT, RP_BTN_RIGHT, RP_BTN_B, RP_BTN_A, RP_BTN_SELECT, RP_BTN_START, RP_BTN_MENU, SLOT_NONE, SLOT_NONE, SLOT_NONE, SLOT_NONE},
    /*  3 SNES: UP=PD1, DOWN=PD2, LEFT=PD3, RIGHT=PD4, X=PD5, B=PD6, Y=PD7, A=PC0, SELECT=PC1, START=PC2, MENU=PC3, L=PF0, R=PF1 */
    [3] = {RP_BTN_UP, RP_BTN_DOWN, RP_BTN_LEFT, RP_BTN_RIGHT, RP_BTN_X, RP_BTN_B, RP_BTN_Y, RP_BTN_A, RP_BTN_SELECT, RP_BTN_START, RP_BTN_MENU, RP_BTN_L, RP_BTN_R},
    /*  4 same slots as the NES / Game Boy / Master System board: UP=PD1, DOWN=PD2, LEFT=PD3, RIGHT=PD4, B=PD5, A=PD6, SELECT=PD7, START=PC0, MENU=PC1 */
    [4] = {RP_BTN_UP, RP_BTN_DOWN, RP_BTN_LEFT, RP_BTN_RIGHT, RP_BTN_B, RP_BTN_A, RP_BTN_SELECT, RP_BTN_START, RP_BTN_MENU, SLOT_NONE, SLOT_NONE, SLOT_NONE, SLOT_NONE},
    /*  5 Genesis / Mega Drive 6-button: UP=PD1, DOWN=PD2, LEFT=PD3, RIGHT=PD4, A=PD5, X=PD6, B=PD7, Y=PC0, C=PC1, Z=PC2, MODE=PC3, START=PF0, MENU=PF1 */
    [5] = {RP_BTN_UP, RP_BTN_DOWN, RP_BTN_LEFT, RP_BTN_RIGHT, RP_BTN_A, RP_BTN_X, RP_BTN_B, RP_BTN_Y, RP_BTN_C, RP_BTN_Z, RP_BTN_SELECT, RP_BTN_START, RP_BTN_MENU},
    /*  6 no board layout yet: generic slot order UP DOWN LEFT RIGHT A B X Y L R SELECT START MENU */
    [6] = {RP_BTN_UP, RP_BTN_DOWN, RP_BTN_LEFT, RP_BTN_RIGHT, RP_BTN_A, RP_BTN_B, RP_BTN_X, RP_BTN_Y, RP_BTN_L, RP_BTN_R, RP_BTN_SELECT, RP_BTN_START, RP_BTN_MENU},
    /*  7 no board layout yet: generic slot order UP DOWN LEFT RIGHT A B X Y L R SELECT START MENU */
    [7] = {RP_BTN_UP, RP_BTN_DOWN, RP_BTN_LEFT, RP_BTN_RIGHT, RP_BTN_A, RP_BTN_B, RP_BTN_X, RP_BTN_Y, RP_BTN_L, RP_BTN_R, RP_BTN_SELECT, RP_BTN_START, RP_BTN_MENU},
    /*  8 no board layout yet: generic slot order UP DOWN LEFT RIGHT A B X Y L R SELECT START MENU */
    [8] = {RP_BTN_UP, RP_BTN_DOWN, RP_BTN_LEFT, RP_BTN_RIGHT, RP_BTN_A, RP_BTN_B, RP_BTN_X, RP_BTN_Y, RP_BTN_L, RP_BTN_R, RP_BTN_SELECT, RP_BTN_START, RP_BTN_MENU},
    /*  9 no board layout yet: generic slot order UP DOWN LEFT RIGHT A B X Y L R SELECT START MENU */
    [9] = {RP_BTN_UP, RP_BTN_DOWN, RP_BTN_LEFT, RP_BTN_RIGHT, RP_BTN_A, RP_BTN_B, RP_BTN_X, RP_BTN_Y, RP_BTN_L, RP_BTN_R, RP_BTN_SELECT, RP_BTN_START, RP_BTN_MENU},
    /* 10 no board layout yet: generic slot order UP DOWN LEFT RIGHT A B X Y L R SELECT START MENU */
    [10] = {RP_BTN_UP, RP_BTN_DOWN, RP_BTN_LEFT, RP_BTN_RIGHT, RP_BTN_A, RP_BTN_B, RP_BTN_X, RP_BTN_Y, RP_BTN_L, RP_BTN_R, RP_BTN_SELECT, RP_BTN_START, RP_BTN_MENU},
    /* 11 no board layout yet: generic slot order UP DOWN LEFT RIGHT A B X Y L R SELECT START MENU */
    [11] = {RP_BTN_UP, RP_BTN_DOWN, RP_BTN_LEFT, RP_BTN_RIGHT, RP_BTN_A, RP_BTN_B, RP_BTN_X, RP_BTN_Y, RP_BTN_L, RP_BTN_R, RP_BTN_SELECT, RP_BTN_START, RP_BTN_MENU},
    /* 12 no board layout yet: generic slot order UP DOWN LEFT RIGHT A B X Y L R SELECT START MENU */
    [12] = {RP_BTN_UP, RP_BTN_DOWN, RP_BTN_LEFT, RP_BTN_RIGHT, RP_BTN_A, RP_BTN_B, RP_BTN_X, RP_BTN_Y, RP_BTN_L, RP_BTN_R, RP_BTN_SELECT, RP_BTN_START, RP_BTN_MENU},
    /* 13 no board layout yet: generic slot order UP DOWN LEFT RIGHT A B X Y L R SELECT START MENU */
    [13] = {RP_BTN_UP, RP_BTN_DOWN, RP_BTN_LEFT, RP_BTN_RIGHT, RP_BTN_A, RP_BTN_B, RP_BTN_X, RP_BTN_Y, RP_BTN_L, RP_BTN_R, RP_BTN_SELECT, RP_BTN_START, RP_BTN_MENU},
    /* 14 NES / Game Boy / Master System: UP=PD1, DOWN=PD2, LEFT=PD3, RIGHT=PD4, B=PD5, A=PD6, SELECT=PD7, START=PC0, MENU=PC1 */
    [14] = {RP_BTN_UP, RP_BTN_DOWN, RP_BTN_LEFT, RP_BTN_RIGHT, RP_BTN_B, RP_BTN_A, RP_BTN_SELECT, RP_BTN_START, RP_BTN_MENU, SLOT_NONE, SLOT_NONE, SLOT_NONE, SLOT_NONE},
    /* 15 no board layout yet: generic slot order UP DOWN LEFT RIGHT A B X Y L R SELECT START MENU */
    [15] = {RP_BTN_UP, RP_BTN_DOWN, RP_BTN_LEFT, RP_BTN_RIGHT, RP_BTN_A, RP_BTN_B, RP_BTN_X, RP_BTN_Y, RP_BTN_L, RP_BTN_R, RP_BTN_SELECT, RP_BTN_START, RP_BTN_MENU},
};

/* Console-select board (NES / Game Boy / Master System): straps read SELECT_STRAP_ID; the select button
 * (PC3) steps through select_console[], shown on the status LED (PC2) in GRB. */
#define SELECT_STRAP_ID 14
#define SELECT_COUNT 3
static const uint8_t select_console[SELECT_COUNT] = {1 /* NES */, 2 /* GB */, 4 /* SMS */};
static const uint8_t select_grb[SELECT_COUNT][3] = {{0, 40, 0}, {40, 0, 0}, {0, 0, 40}};

#endif /* RETROPAD_PINMAP_H */

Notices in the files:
hardware/tab5_controller/firmware_avrdd/main.c:
SPDX-License-Identifier: MIT
